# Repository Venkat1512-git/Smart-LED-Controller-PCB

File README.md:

# Smart LED Controller PCB

## Overview

This project is a custom-designed Smart LED Controller built around the ATmega328P microcontroller. The project demonstrates the complete embedded hardware development workflow, from schematic capture and PCB layout to firmware development and manufacturing file generation.

## Features

- ATmega328P Microcontroller
- Custom PCB designed in KiCad
- Five LED outputs
- Three Push Button Inputs
- ISP Programming Header
- 16 MHz Crystal Oscillator
- Gerber Files for PCB Manufacturing
- Embedded C Firmware (Coming Soon)

---

## Hardware

- ATmega328P-PU
- 16 MHz Crystal
- 5 LEDs
- 3 Push Buttons
- Resistors
- Capacitors
- ISP Header

---

## Software

- KiCad
- Embedded C
- GitHub

---

## Project Structure

```
Smart-LED-Controller-PCB
│
├── Hardware
├── Firmware
├── Gerber
├── Images
├── Documentation
└── README.md
```

---

## Project Status

- [x] Schematic Design
- [x] PCB Layout
- [x] DRC Passed (0 Errors)
- [x] Gerber Files Generated
- [ ] Firmware Development
- [ ] Hardware Testing

---

## Author

**Venkata Subbaiah Chakali**

Electrical & Embedded Systems Engineer

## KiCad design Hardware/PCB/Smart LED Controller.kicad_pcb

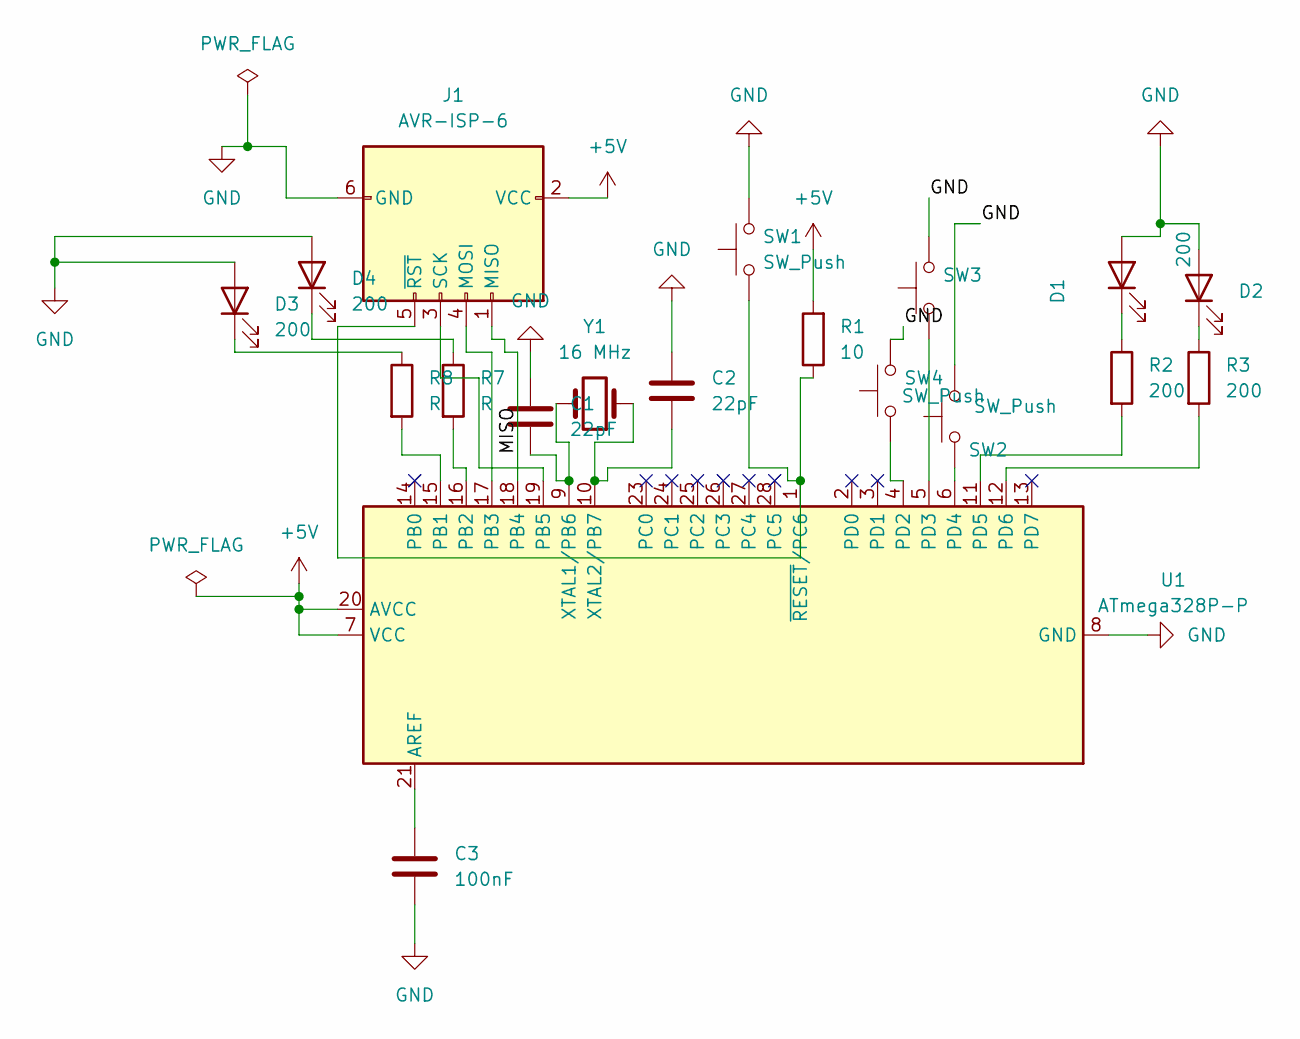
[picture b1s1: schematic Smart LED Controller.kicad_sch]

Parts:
C1, C2: 22pF; C_Disc_D5.0mm_W2.5mm_P5.00mm
C3: 100nF; C_Disc_D5.0mm_W2.5mm_P5.00mm
D1, D2, D3, D4: 200; LED_D5.0mm
J1: AVR-ISP-6; PinHeader_2x03_P2.54mm_Vertical
R1: 10; R_Axial_DIN0207_L6.3mm_D2.5mm_P7.62mm_Horizontal
R2, R3: 200; R_Axial_DIN0207_L6.3mm_D2.5mm_P7.62mm_Horizontal
R7, R8: R; R_Axial_DIN0207_L6.3mm_D2.5mm_P7.62mm_Horizontal
SW1, SW2, SW3, SW4: SW_Push; SW_PUSH_6mm
U1: ATmega328P-P; DIP-28_W7.62mm
Y1: 16 MHz; Crystal_HC49-U_Vertical

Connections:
+5V: J1.2 (VCC), R1.2, U1.7 (VCC), U1.20 (AVCC)
/MISO: J1.1 (MISO), U1.18 (PB4)
GND: C1.2, C2.1, C3.2, D1.2 (A), D2.2 (A), D3.2 (A), D4.2 (A), J1.6 (GND), SW1.2, SW2.2, SW3.2, SW4.2, U1.8 (GND), U1.22 (GND)
unnamed: D1.1 (K), R2.1
unnamed: D2.1 (K), R3.1
unnamed: D3.1 (K), R8.1
unnamed: D4.1 (K), R7.1
unnamed: J1.4 (MOSI), U1.17 (PB3)
unnamed: J1.3 (SCK), U1.19 (PB5)
unnamed: J1.5 (~RST), R1.1, SW1.1, U1.1 (~RESET/PC6)
unnamed: C3.1, U1.21 (AREF)
unnamed: R8.2, U1.15 (PB1)
unnamed: R7.2, U1.16 (PB2)
unnamed: SW4.1, U1.4 (PD2)
unnamed: SW3.1, U1.5 (PD3)
unnamed: SW2.1, U1.6 (PD4)
unnamed: R2.2, U1.11 (PD5)
unnamed: R3.2, U1.12 (PD6)
unnamed: C1.1, U1.9 (XTAL1/PB6), Y1.2
unnamed: C2.2, U1.10 (XTAL2/PB7), Y1.1

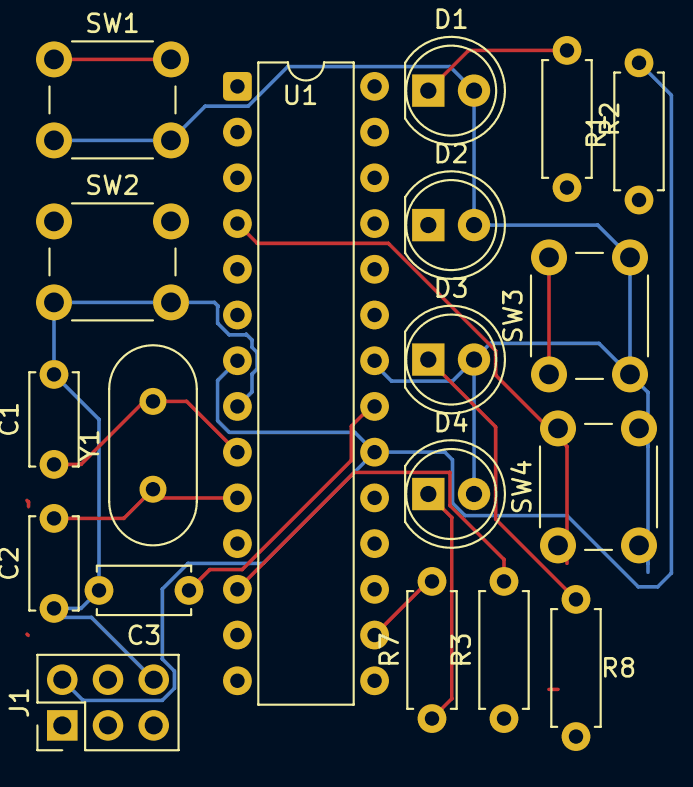
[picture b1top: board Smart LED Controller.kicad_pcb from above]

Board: 2 copper layers, 19 parts (0 on the bottom side), 20 nets.
